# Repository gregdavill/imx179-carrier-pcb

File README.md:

# Sony IMX179 Breakout

## A breakout for the Sony IMX179 8MP CMOS Sensor

## Hardware

* Sony IMX179 Sensor
* 1V2, 1V8, 2V5 LDO Voltage rails
* MEMS Oscillator
* 20 pin FFC connector to host system

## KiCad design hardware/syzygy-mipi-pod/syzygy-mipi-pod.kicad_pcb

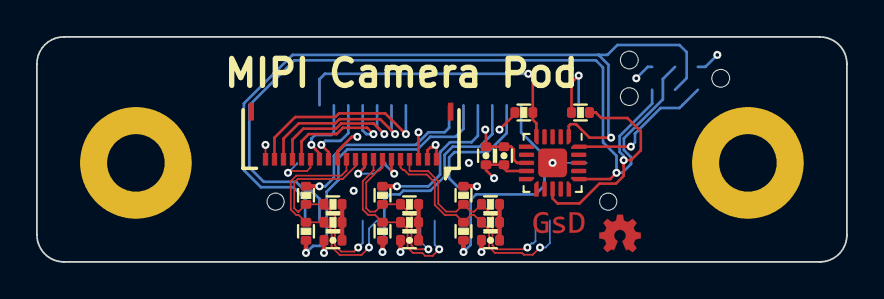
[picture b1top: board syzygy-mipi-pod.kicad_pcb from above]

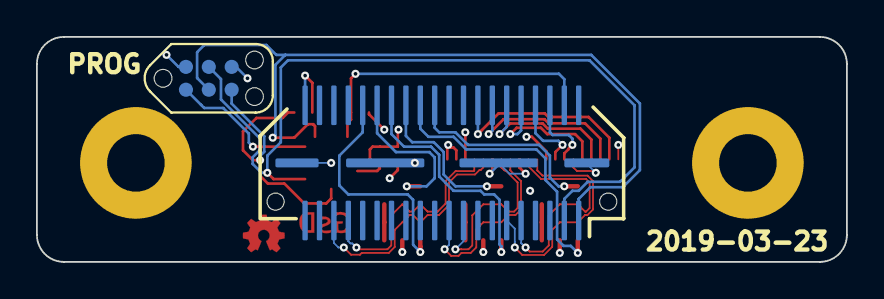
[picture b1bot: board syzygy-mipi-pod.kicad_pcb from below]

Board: 4 copper layers, 45.0 x 12.5 mm, 23 parts (2 on the bottom side), 28 nets.

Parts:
C1, C2, C3: 100pF; C_0402
C14: 100nF; C_0402
C15: 1uF; C_0402
J1: SYZYGY-STD; SYZYGY_standard_pod
J2: Conn_01x20; 5034802000
J3: TagConnect; TC2030-NL_SMALL
R1, R14: 10K; R_0402
R2, R3, R4, R5, R6, R7: 150R; R_0402
R8, R9, R10, R11, R12, R13: 100R; R_0402
U1: ATtiny44A-MMH; QFN-20-1EP_3x3mm_P0.45mm_EP1.6x1.6mm

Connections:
+3V3: C14.1, C15.1, J1.40, J2.1, J2.2, J3.2, R1.1, R14.1, U1.9
/CAM0_CLK_N: J1.35, J2.5, R3.1, R9.2
/CAM0_CLK_P: J1.33, J2.4, R2.2, R8.2
/CAM0_D0_N: J1.19, J2.8, R5.1, R11.2
/CAM0_D0_P: J1.17, J2.7, R4.2, R10.2
/CAM0_D1_N: J1.11, J2.11, R7.1, R13.2
/CAM0_D1_P: J1.9, J2.10, R6.2, R12.2
/CAM0_SCL: J1.6, J2.14
/CAM0_SDA: J1.8, J2.13
/GPIO0: J1.10, J2.16
/GPIO1: J1.12, J2.17
/GPIO2: J1.14, J2.18
/GPIO3: J1.16, J2.19
/Peripheral MCU/MISO: J3.1, U1.20
/Peripheral MCU/~RESET: J3.5, R14.2, U1.13
/RGA: J1.4, R1.2, U1.5
/SCL: J1.1, J3.3, U1.1
/SDA: J1.3, J3.4, U1.16
/TERM_0_N: J1.28, R11.1
/TERM_0_P: J1.26, R10.1
/TERM_1_N: J1.24, R13.1
/TERM_1_P: J1.22, R12.1
/TERM_CLK_N: J1.32, R9.1
/TERM_CLK_P: J1.30, R8.1
GND: C1.2, C2.2, C3.2, C14.2, C15.2, J1.41, J2.3, J2.6, J2.9, J2.12, J2.15, J2.20, J3.6, U1.8, U1.21
unnamed: C1.1, R2.1, R3.2
unnamed: C2.1, R4.1, R5.2
unnamed: C3.1, R6.1, R7.2

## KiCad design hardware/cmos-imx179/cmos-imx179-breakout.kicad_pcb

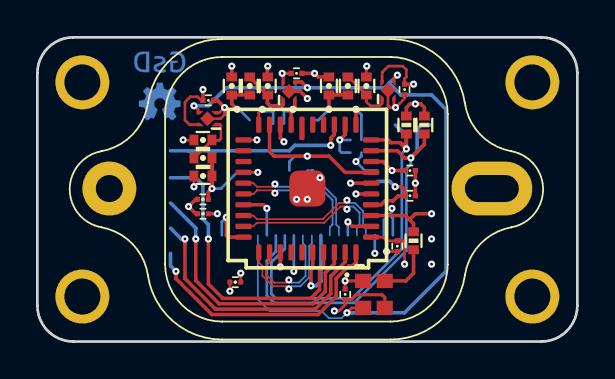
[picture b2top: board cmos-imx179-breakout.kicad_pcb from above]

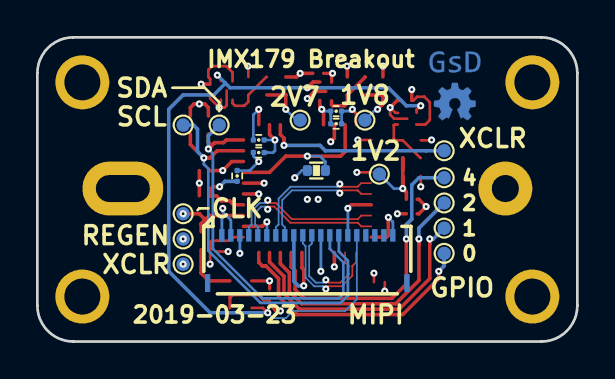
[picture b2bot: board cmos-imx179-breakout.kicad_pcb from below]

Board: 4 copper layers, 30.0 x 16.9 mm, 34 parts (7 on the bottom side), 20 nets.

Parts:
C1, C3, C5, C9, C10, C11: 1uF; C_0402
C7, C12, C13, C14, C15, C16, C17, C18, C19, C20, C21, C22, C23, C24, C25: 100nF; C_0201
J1: Conn_01x20; 5034802000
L1, L2, L3: 600R; C_0402
R1, R2: 2.2K; R_0402
R3: 22R; R_0402
R4: 0R; R_0402
U1: NCP114-120; X2SON_4_1.0x1.0mm
U2: NCP167-180; X2SON_4_1.0x1.0mm
U3: imx179-plcc40; PLCC-40_sony
U4: NCP167-270; X2SON_4_1.0x1.0mm
U5: 24.00 MHz; CDFN3225-4LD-PL-1

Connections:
+1V2: C5.1, C7.1, C18.1, C22.1, C23.1, C24.1, C25.1, L1.1, U3.5, U3.26, U3.37
+1V8: C10.1, C12.1, C13.1, C19.1, C20.1, C21.1, L2.1, R1.1, R2.1, U3.29, U5.1
+2V7: C11.1, C14.1, L3.1, U3.3, U3.33
+3V3: C15.1, C16.1, C17.1, J1.1, J1.2, U1.4, U2.4, U4.4
/AGND: R4.1, U3.4, U3.32
/CAM_SCL: J1.14, R1.2, U3.34
/CAM_SDA: J1.13, R2.2, U3.35
/CLK_IN: R3.2, U3.28
/CLK_N: J1.5, U3.14
/CLK_P: J1.4, U3.13
/DATA0_N: J1.8, U3.11
/DATA0_P: J1.7, U3.10
/DATA1_N: J1.11, U3.17
/DATA1_P: J1.10, U3.16
/ENABLE: J1.16, U1.3, U2.3, U4.3, U5.2
GND: C1.2, C3.2, C5.2, C7.2, C9.2, C10.2, C11.2, C12.2, C13.2, C14.2, C15.2, C16.2, C17.2, C18.2, C19.2, C20.2, C21.2, C22.2, C23.2, C24.2, C25.2, J1.3, J1.6, J1.9, J1.12, J1.15, J1.20, R4.2, U1.2, U2.2, U3.2, U3.6, U3.9, U3.12, U3.15, U3.18, U3.21, U3.27, U3.36, U3.41, U4.2, U5.3
unnamed: C1.1, L2.2, U2.1
unnamed: C3.1, L1.2, U1.1
unnamed: C9.1, L3.2, U4.1
unnamed: R3.1, U5.4

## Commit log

2019-03-22 Fixed up submodules
2019-03-23 Updated CMOS IMX179 Breakout
2019-03-23 Added new project: SYZYGY to MIPI RX Pod
